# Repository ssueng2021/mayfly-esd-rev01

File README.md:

# mayfly-esd-rev01
 
 Mayfly Analog ESD wing board
 
 2022-March-02 files updated for Kicad 6.0 https://www.kicad.org/blog/

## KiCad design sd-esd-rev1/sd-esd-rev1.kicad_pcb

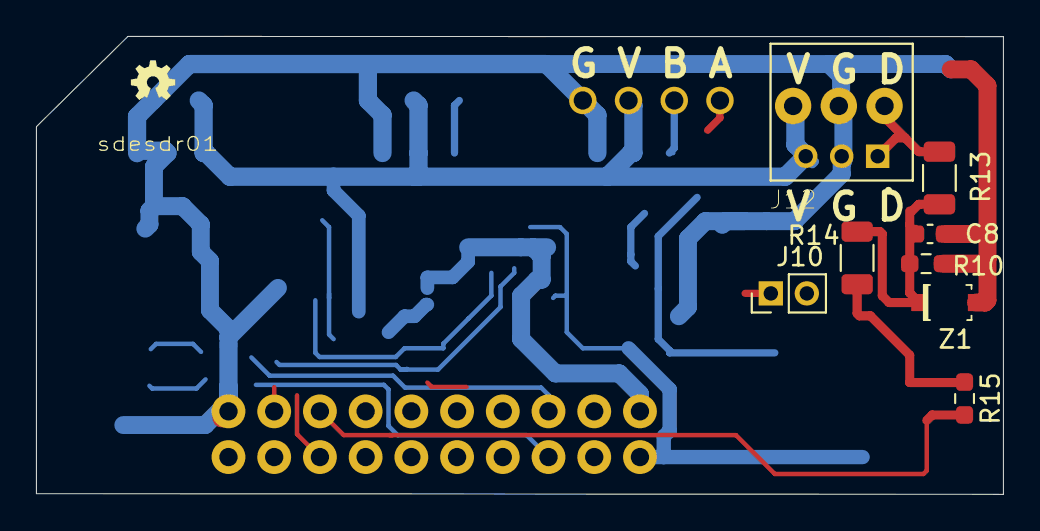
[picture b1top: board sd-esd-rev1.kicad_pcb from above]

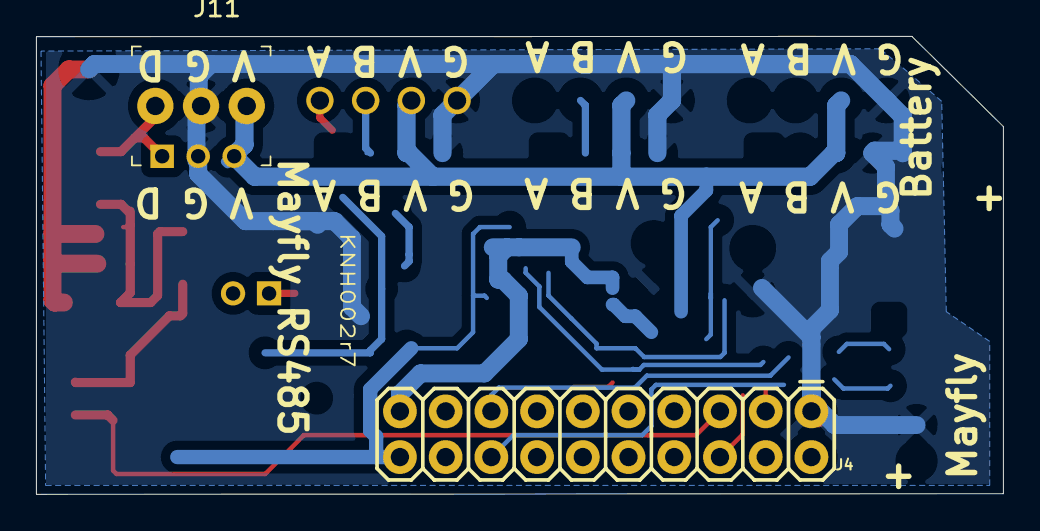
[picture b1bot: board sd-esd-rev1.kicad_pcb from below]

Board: 2 copper layers, 53.7 x 25.4 mm, 12 parts (2 on the bottom side), 5 nets.

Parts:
C8: 3300pF; C_0603_1608Metric
J4: CONN_10X2; 2X10
J7: CONN_42.54_NOSILK; 1X04_NOSILK
J10: 2mm jumper; PinHeader_1x02_P2.00mm_Vertical
J11: WireTerm; PinHeader_1x3_P2.54mm_Drill1.02mm
J12: S3B-PH-K-S(LF)(SN); JST_S3B-PH-K-S(LF)(SN)
LOGO1: OSHW-LOGOMINI; OSHW-LOGO-MINI
R10: 200K; R_0603_1608Metric_Pad0.98x0.95mm_HandSolder
R13, R14: 510R; R_1206_3216Metric
R15: zero; R_0603_1608Metric_Pad0.98x0.95mm_HandSolder
Z1: 7.5V; SOD-123

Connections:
+12V: J11.3, J12.3
GND: C8.2, J4.1, J7.4, J11.2, J12.2, R10.1, Z1.A
unnamed: C8.1, R10.2, R13.1, R14.2, Z1.K
unnamed: J11.1, J12.1, R13.2
unnamed: R14.1, R15.1

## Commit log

2021-12-25 Initial commit
    Initial files for framework for Mayfly Wingboard - based off the Digital connectors, needs to be changed to Analog connector
2022-03-02 Updated for kicad 6.0 https://www.kicad.org/blog/
